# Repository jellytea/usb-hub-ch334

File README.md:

# usb-hub-ch334
USB 2.0 HighSpeed hub with CH334.

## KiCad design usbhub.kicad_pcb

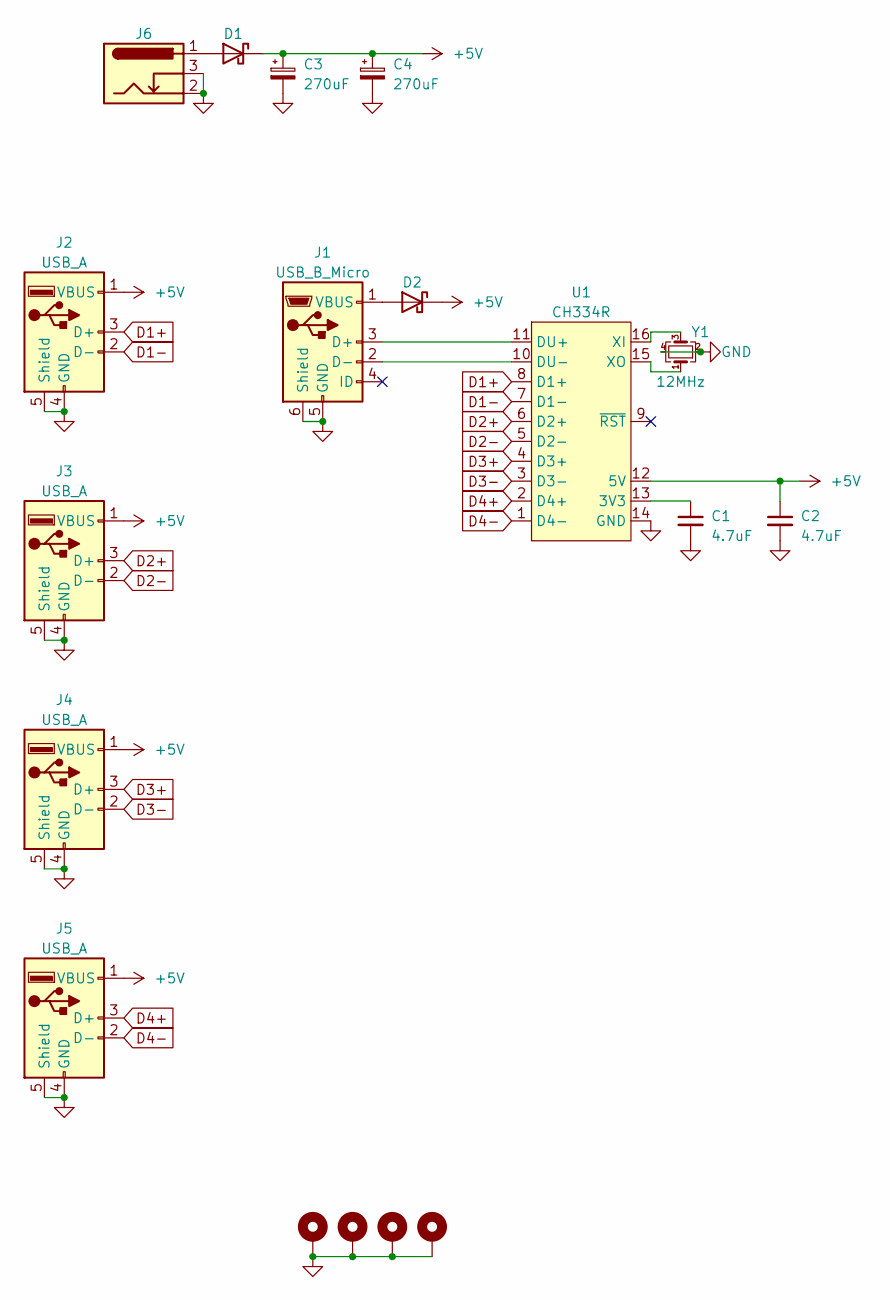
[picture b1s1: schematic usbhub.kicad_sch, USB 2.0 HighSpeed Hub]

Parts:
C1, C2: 4.7uF; C_0805_2012Metric
C3, C4: 270uF; CP_Radial_D5.0mm_P2.50mm
D1, D2: D_Schottky; D_SMA
H1, H2, H3, H4: MountingHole_Pad; MountingHole_3.5mm_Pad_Via
J1: USB_B_Micro; USB_Micro-B_Amphenol_10118194_Horizontal
J2, J3, J4, J5: USB_A; USB_A_Stewart_SS-52100-001_Horizontal
J6: Barrel_Jack_Switch; BarrelJack_Horizontal
U1: CH334R; QSOP-16_3.9x4.9mm_P0.635mm
Y1: 12MHz; Crystal_SMD_3225-4Pin_3.2x2.5mm

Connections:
+5V: C2.1, C3.1, C4.1, D1.1 (K), D2.1 (K), J2.1 (VBUS), J3.1 (VBUS), J4.1 (VBUS), J5.1 (VBUS), U1.12 (5V)
D1+: J2.3 (D+), U1.8 (D1+)
D1-: J2.2 (D-), U1.7 (D1-)
D2+: J3.3 (D+), U1.6 (D2+)
D2-: J3.2 (D-), U1.5 (D2-)
D3+: J4.3 (D+), U1.4 (D3+)
D3-: J4.2 (D-), U1.3 (D3-)
D4+: J5.3 (D+), U1.2 (D4+)
D4-: J5.2 (D-), U1.1 (D4-)
GND: C1.2, C2.2, C3.2, C4.2, H1.1, H2.1, H3.1, H4.1, J1.5 (GND), J1.6 (Shield), J2.4 (GND), J2.5 (Shield), J3.4 (GND), J3.5 (Shield), J4.4 (GND), J4.5 (Shield), J5.4 (GND), J5.5 (Shield), J6.2, J6.3, U1.14 (GND), Y1.2, Y1.4
unnamed: D1.2 (A), J6.1
unnamed: D2.2 (A), J1.1 (VBUS)
unnamed: J1.3 (D+), U1.11 (DU+)
unnamed: J1.2 (D-), U1.10 (DU-)
unnamed: C1.1, U1.13 (3V3)
unnamed: U1.16 (XI), Y1.3
unnamed: U1.15 (XO), Y1.1

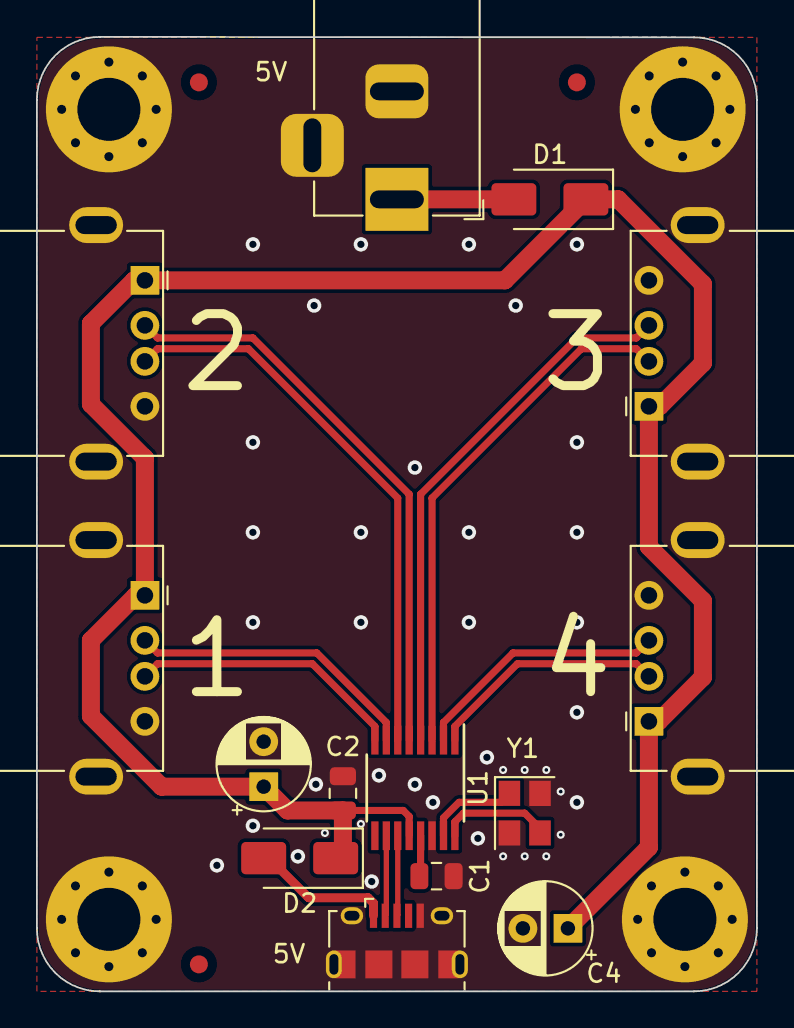
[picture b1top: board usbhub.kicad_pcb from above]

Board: 2 copper layers, 40.0 x 53.0 mm, 18 parts (0 on the bottom side), 17 nets.

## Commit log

2023-12-27 Revision 1.0

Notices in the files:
usbhub.kicad_pcb:
https://creativecommons.org/licenses/by-sa/4.0/legalcode.en
Use of this PCB design is governed under the CC BY-SA 4.0 International license.
© 2023 JetERA Creative
B.SilkS
usbhub.kicad_sch:
Use of this schematic is governed under the CC BY-SA 4.0 International license.
